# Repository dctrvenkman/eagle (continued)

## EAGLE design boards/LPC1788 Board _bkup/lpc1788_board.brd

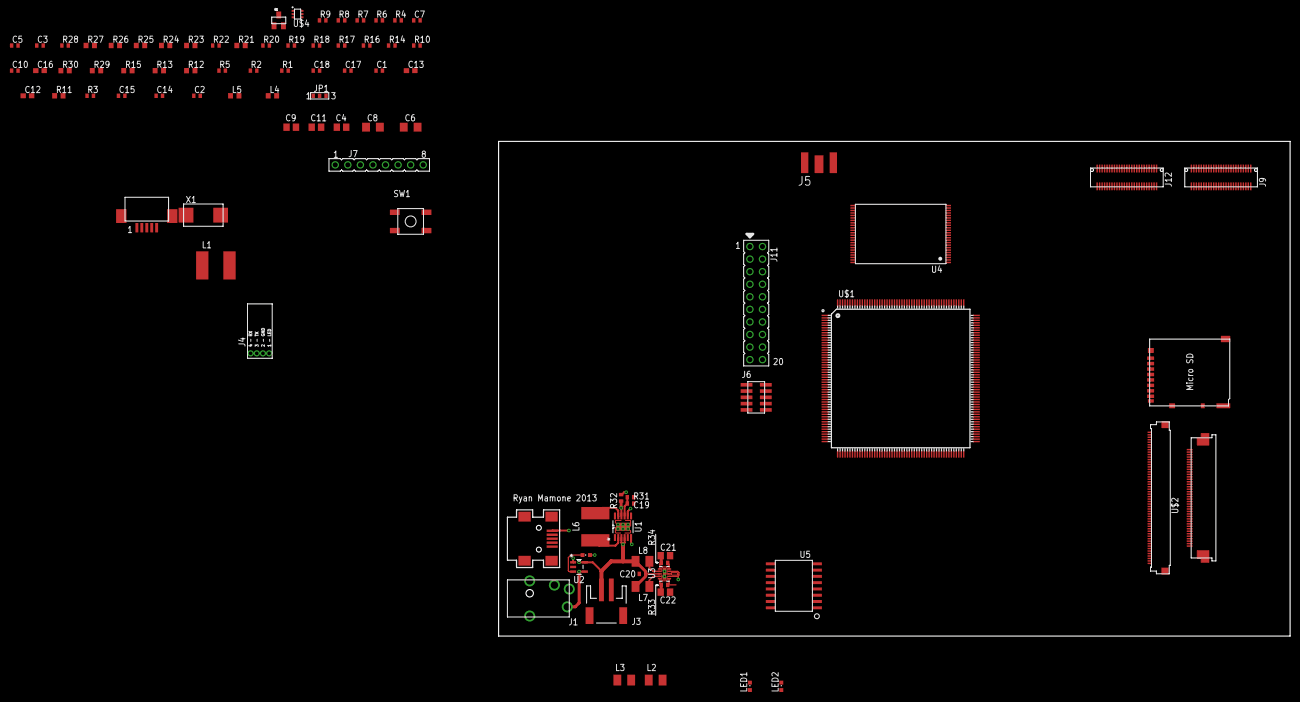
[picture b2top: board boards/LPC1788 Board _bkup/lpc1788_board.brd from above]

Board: 2 copper layers, 160.0 x 100.0 mm, 92 parts (0 on the bottom side), 154 nets.

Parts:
C1: 10uF; C0402
C2, C19: 100pF; C0402
C3, C5, C7, C10, C20: 1uF; C0402
C4: 22uF; C0805
C6: 100uF; C1206
C8: 330uF; C1206
C9, C11, C21, C22: 1uF; C0805
C12, C13: 18pF; C0603
C14, C15: 100nF; C0402
C16: .1uF; C0603
C17, C18: 18pF; C0402
J1: 5VDC; PJ-045
J2: SAMTEC_MUSB; MUSB-05-X-B-SM-A
J3: JST_2MM_SMT
J4: Console; 4-PIN_1.25MM
J5: SMA-J-P-X-ST-EM1
J6: JTAG; 10-PIN_5X2_.050IN_SMT
J7: JTAG; 8-PIN_SIP_.100IN
J8: NHD-4.3-480272EF; FCI_62684-402100ALF
J9, J12: DF12B-50DX_25X2_0.5MM
J10: MOLEX_527930570_5PIN_FFC_CONNECTOR; MOLEX_527930570
J11: 20PIN_10X2_.100IN; 20-PIN_10X2_.100IN
JP1: RESISTOR_JUMPER_0402
L1, L6: 4.7uH; NR6028
L2, L3, L7, L8: 15uH; L3225M
L4, L5: 470nH; 0603
LED1, LED2, LED3: CHG; CHIPLED_0603
Q1: MMBT2907; SOT23
R1, R32: 320k; R0402
R2: 182k; R0402
R3: 32.4k; R0402
R4, R16: 50; R0402
R5, R31: 499k; R0402
R6, R7, R33, R34: 10; R0402
R8, R9, R10: 0; R0402
R11: 100K; R0603
R12, R13, R29, R30: 4.7K; R0603
R14, R19, R20, R22, R28: 10k; R0402
R15: 1.5K; R0603
R17, R18: 33; R0402
R21: 0; R0603
R23, R24, R25, R26, R27: 10K; R0603
SW1: Reset; SMT_PUSHBUTTON
U1: LTC3127EMSEPBF; SOP65P490X110-13N
U2: MAX1551EZK+T; SOT95P275X110-5N
U3: LT3497EDDBTRMPBF; DFN300X200X80-11N
U4: CY62167_16MBIT_SRAM; TSOP48
U5: S25FL064P; SO3_016
U$1: LPC177X_8X-208; LQFP208
U$2: NHD-3.5-320240MF; MOLEX_51296-5494
U$3: DM3AT
U$4: NUP2202; SC-88
X1: 12MHz; 2-SMD_8MMX4.5MM

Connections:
!BLS0: U4.15, U$1.119
!BLS1: U4.14, U$1.139
!CS0: U4.26, U$1.187
!OE: U4.28, U$1.183
!WE: U4.11, U$1.179
+3V1: R32.2, U1.10
+3V3: C4.1, C6.1, C8.1, J4.1, J6.P$1, J8.P$4, J9.P$1, J9.P$2, J10.P$1, J11.1, J11.2, J11.3, J11.4, J12.P$1, J12.P$2, L4.1, L5.1, Q1.2, R1.2, R11.2, R12.1, R13.1, R14.1, R16.2, R19.1, R20.1, R21.2, R22.1, R23.1, R25.1, R26.1, R27.1, R28.1, R29.1, R30.1, U4.37, U5.P$2, U$1.15, U$1.26, U$1.60, U$1.71, U$1.86, U$1.89, U$1.112, U$1.125, U$1.146, U$1.165, U$1.174, U$1.181, U$1.198, U$2.P$41, U$2.P$42, U$3.VDD
+VBAT: C1.1, C7.1, C10.1, L2.1, L3.1, R4.2
+VBAT1: C20.1, J3.2, L7.1, L8.1, U1.3, U1.4, U2.5, U3.8
+VUSB: C5.1, U$4.P$5
+VUSB1: J2.1, U2.1
/RESET: C16.1, J6.P$10, J7.6, R11.1, SW1.P$1, SW1.P$2, U$1.35
A0: U4.25, U$1.75
A1: U4.24, U$1.79
A2: U4.23, U$1.83
A3: U4.22, U$1.97
A4: U4.21, U$1.103
A5: U4.20, U$1.107
A6: U4.19, U$1.113
A7: U4.18, U$1.121
A8: U4.8, U$1.127
A9: U4.7, U$1.131
A10: U4.6, U$1.135
A11: U4.5, U$1.145
A12: U4.4, U$1.149
A13: U4.3, U$1.155
A14: U4.2, U$1.159
A15: U4.1, U$1.173
A16: U4.48, U$1.101
A17: U4.17, U$1.104
A18: U4.16, U$1.105
A19: U4.9, U$1.111
B0: J8.P$21, U$1.160, U$2.P$12
B1: J8.P$22, U$1.158, U$2.P$13
B2: J8.P$23, U$1.106, U$2.P$14
B3: J8.P$24, U$1.102, U$2.P$15
B4: J8.P$25, U$1.82, U$2.P$16
B5: J8.P$26, U$1.88, U$2.P$17
B6: J8.P$27, U$1.90, U$2.P$18
B7: J8.P$28, U$1.92, U$2.P$19
D0: U4.29, U$1.197
D1: U4.31, U$1.201
D2: U4.33, U$1.207
D3: U4.35, U$1.3
D4: U4.38, U$1.13
D5: U4.40, U$1.17
D6: U4.42, U$1.23
D7: U4.44, U$1.27
D8: U4.30, U$1.191
D9: U4.32, U$1.199
D10: U4.34, U$1.205
D11: U4.36, U$1.208
D12: U4.39, U$1.1
D13: U4.41, U$1.7
D14: U4.43, U$1.21
D15: U4.45, U$1.28
EXT_UART_RX: J11.16, U$1.100
EXT_UART_TX: J11.14, U$1.98
G0: J8.P$13, U$1.164, U$2.P$20
G1: J8.P$14, U$1.162, U$2.P$21
G2: J8.P$15, U$1.170, U$2.P$22
G3: J8.P$16, U$1.176, U$2.P$23
G4: J8.P$17, U$1.74, U$2.P$24
G5: J8.P$18, U$1.76, U$2.P$25
G6: J8.P$19, U$1.78, U$2.P$26
G7: J8.P$20, U$1.80, U$2.P$27
GND: C1.2, C2.2, C3.2, C4.2, C5.2, C6.2, C7.2, C8.2, C9.2, C10.2, C11.2, C12.2, C13.2, C14.2, C15.2, C16.2, C17.2, C18.2, J4.2, J5.G@1, J6.P$3, J6.P$5, J6.P$9, J7.8, J8.P$1, J8.P$3, J8.P$29, J8.P$36, J9.P$49, J9.P$50, J10.P$5, J11.17, J11.18, J11.19, J11.20, J12.P$49, J12.P$50, R2.1, R3.1, R5.1, R24.2, SW1.P$3, SW1.P$4, U4.27, U4.46, U5.P$10, U$1.22, U$1.32, U$1.33, U$1.63, U$1.77, U$1.84, U$1.93, U$1.114, U$1.133, U$1.148, U$1.169, U$1.172, U$1.189, U$1.200, U$2.P$1, U$2.P$2, U$2.P$53, U$2.P$54, U$3.DET_B, U$3.VSS, U$4.P$2
GND1: C19.2, C20.2, C21.2, C22.2, J1.2, J1.3, J2.5, J3.1, R31.1, U1.1, U1.5, U1.7, U1.12, U1.13, U2.2, U3.3, U3.11
KEY_I2C_SCL: J10.P$3, R30.2, U$1.48
KEY_I2C_SDA: J10.P$2, R29.2, U$1.50
KEY_INT: J10.P$4, U$1.61
LCD_DCLK: J8.P$30, U$1.150, U$2.P$38
LCD_ENAB_M: J8.P$34, R8.1, U$1.142
LCD_FP: J8.P$33, U$1.144, U$2.P$37
LCD_LE: R9.1, U$1.152
LCD_LP: J8.P$32, U$1.140, U$2.P$36
LCD_PWR: R10.1, U$1.154
LED1_PWR: J8.P$2, JP1.1, R6.1, U$2.P$3
LED2_PWR: JP1.3, R7.1
LED+1: JP1.2, U$2.P$4
unnamed: R1.1, R2.2
unnamed: C9.1, R6.2
unnamed: C2.1, R5.2
unnamed: LED1.A, R4.1
unnamed: R8.2, U$2.P$52
unnamed: R9.2, U$2.P$50
unnamed: C11.1, R7.2
unnamed: R10.2, U$2.P$51
unnamed: C12.1, U$1.46, X1.2
unnamed: C13.1, U$1.44, X1.1
unnamed: C14.1, L4.2, U$1.20
unnamed: C15.1, L5.2, U$1.24
unnamed: R18.1, U$4.P$6
unnamed: R17.1, U$4.P$1
unnamed: Q1.3, R15.2
unnamed: Q1.1, U$1.69
unnamed: LED2.A, R16.1
unnamed: LED2.C, U$1.45
unnamed: J4.3, U$1.94
unnamed: J4.4, U$1.96
unnamed: J5.1, U$1.12
unnamed: R19.2, U4.12
unnamed: R20.2, U4.47
unnamed: J11.13, U$1.206
unnamed: R22.2, U5.P$9
unnamed: J11.7, U$1.30
unnamed: R28.2, U5.P$1
unnamed: J11.5, U$1.9
unnamed: J7.1, R21.1
unnamed: R32.1, U1.8
unnamed: C19.1, R31.2, U1.9
unnamed: LED3.C, U2.3
unnamed: L6.2, U1.2
unnamed: L6.1, U1.11
unnamed: C22.1, R33.2, U3.10
unnamed: R33.1, U3.1
unnamed: C21.1, R34.2, U3.6
unnamed: L7.2, U3.9
unnamed: L8.2, U3.7
unnamed: U3.2, U3.4
R0: J8.P$5, U$1.168, U$2.P$28
R1: J8.P$6, U$1.166, U$2.P$29
R2: J8.P$7, U$1.134, U$2.P$30
R3: J8.P$8, U$1.132, U$2.P$31
R4: J8.P$9, U$1.138, U$2.P$32
R5: J8.P$10, U$1.136, U$2.P$33
R6: J8.P$11, U$1.70, U$2.P$34
R7: J8.P$12, U$1.72, U$2.P$35
S$1: R34.1, U3.5
SCL: J11.11, R13.2, U$1.141
SDA: J11.9, R12.2, U$1.117
SD_CLK: U$1.122, U$3.CLK
SD_CMD: U$1.120, U$3.CMD
SD_DAT_0: U$1.116, U$3.DAT0
SD_DAT_1: U$1.153, U$3.DAT1
SD_DAT_2: U$1.163, U$3.DAT2
SD_DAT_3: U$1.157, U$3.CD/DAT3
SD_DET: R14.2, U$3.DET_A
SPI_CS: J11.12, U$1.190
SPI_FLASH_CS: U5.P$7, U$1.130
SPI_FLASH_MISO: U5.P$8, U$1.126
SPI_FLASH_MOSI: U5.P$15, U$1.124
SPI_FLASH_SCK: U5.P$16, U$1.128
SPI_MISO: J11.10, U$1.192
SPI_MOSI: J11.8, U$1.194
SPI_SCK: J11.6, U$1.196
TCK/SWDCLK: J6.P$4, J7.3, R24.1, U$1.10
TDI: J6.P$8, J7.5, R26.2, U$1.4
TDO/SWO: J6.P$6, J7.4, R25.2, U$1.2
TMS/SWDIO: J6.P$2, J7.2, R23.2, U$1.6
TRST: R27.2, U$1.8
USB_D+: C17.1, R15.1, R17.2, U$1.51
USB_D-: C18.1, R18.2, U$1.52
V+1: J1.1, U2.4

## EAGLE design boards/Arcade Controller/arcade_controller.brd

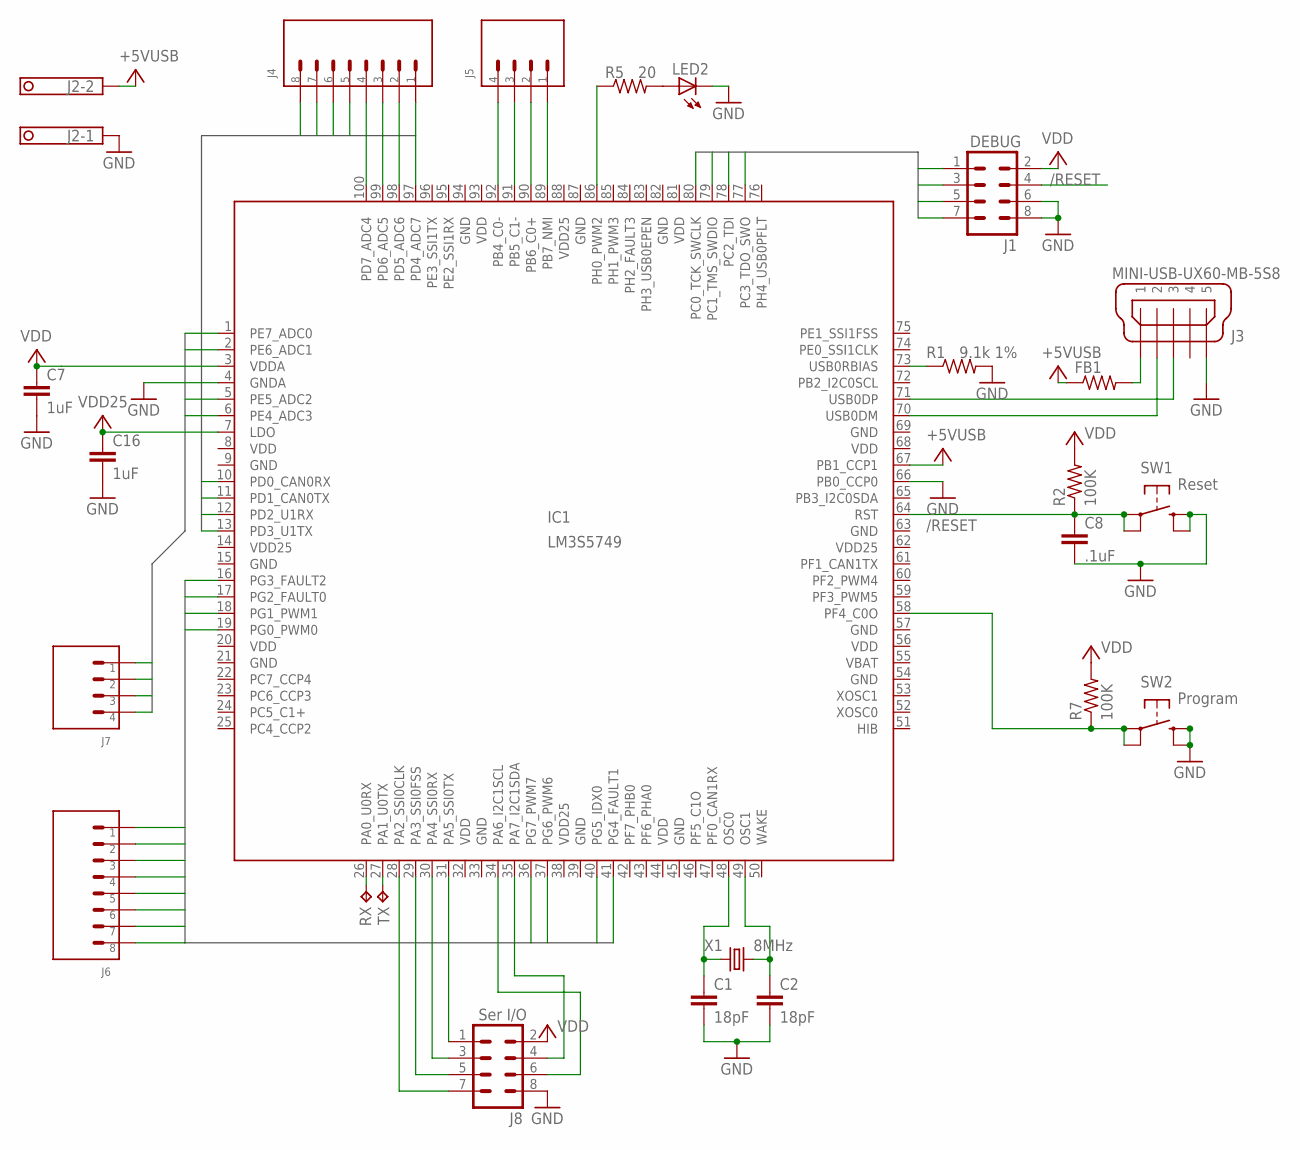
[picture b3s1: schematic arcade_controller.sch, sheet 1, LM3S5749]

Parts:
C1, C2: 18pF; C0603
C7, C16: 1uF; C0603
C8: .1uF; C0603
FB1: 0; R0805
IC1: LM3S5749; LQFP-100
J1: DEBUG; HEADER_.100IN_8PIN_4X2
J2: 1751248
J3: MINI-USB-UX60-MB-5S8; UX60-MB-5S8
J4, J6: PTSM_1771088
J5, J7: PTSM_1702474
J8: Ser I/O; HEADER_.100IN_8PIN_4X2
LED2: LEDCHIPLED_0603; CHIPLED_0603
R1: 9.1k 1%; R0603
R2, R7: 100K; R0603
R5: 20; R0603
RX: TPTP10R; TP10R
SW1: Reset; SMT_PUSHBUTTON
SW2: Program; SMT_PUSHBUTTON
TX: TPTP10R; TP10R
X1: 8MHz; 2-SMD_8MMX4.5MM

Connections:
/PROG: IC1.58 (PF4_C0O), R7.1, SW2.P$1 (P1), SW2.P$2
/RESET: C8.1, IC1.64 (RST), J1.4, R2.1, SW1.P$1 (P1), SW1.P$2
GND: C1.2, C2.2, C7.2, C8.2, C16.2, IC1.4 (GNDA), IC1.9 (GND), IC1.15 (GND), IC1.21 (GND), IC1.33 (GND), IC1.39 (GND), IC1.45 (GND), IC1.54 (GND), IC1.57 (GND), IC1.63 (GND), IC1.66 (PB0_CCP0), IC1.69 (GND), IC1.82 (GND), IC1.87 (GND), IC1.94 (GND), J1.6, J1.8, J2.1, J3.5, J8.8, LED2.C, R1.2, SW1.P$3 (S1), SW1.P$4 (S), SW2.P$3 (S1), SW2.P$4 (S); also elsewhere on the board
unnamed: IC1.73 (USB0RBIAS), R1.1
unnamed: C1.1, IC1.48 (OSC0), X1.1
unnamed: C2.1, IC1.49 (OSC1), X1.2
unnamed: IC1.26 (PA0_U0RX), RX.TP
unnamed: IC1.27 (PA1_U0TX), TX.TP
unnamed: FB1.2, J3.1
unnamed 10: FB1.1, IC1.67 (PB1_CCP1), J2.2; also elsewhere on the board
unnamed: IC1.89 (PB7_NMI), J5.P$1 (S1)
unnamed: IC1.90 (PB6_C0+), J5.P$2 (S2)
unnamed: IC1.91 (PB5_C1-), J5.P$3 (S3)
unnamed: IC1.92 (PB4_C0-), J5.P$4 (S4)
unnamed: IC1.86 (PH0_PWM2), R5.1
unnamed: IC1.31 (PA5_SSI0TX), J8.1
unnamed: LED2.A, R5.2
unnamed: IC1.30 (PA4_SSI0RX), J8.3
unnamed: IC1.71 (USB0DP), J3.3
unnamed: IC1.70 (USB0DM), J3.2
unnamed: IC1.29 (PA3_SSI0FSS), J8.5
unnamed: IC1.28 (PA2_SSI0CLK), J8.7
unnamed: IC1.35 (PA7_I2C1SDA), J8.4
unnamed: IC1.34 (PA6_I2C1SCL), J8.6
PD0: IC1.10 (PD0_CAN0RX), J4.P$1 (S1)
PD1: IC1.11 (PD1_CAN0TX), J4.P$2 (S2)
PD2: IC1.12 (PD2_U1RX), J4.P$3 (S3)
PD3: IC1.13 (PD3_U1TX), J4.P$4 (S4)
PD4: IC1.97 (PD4_ADC7), J4.P$5 (S5)
PD5: IC1.98 (PD5_ADC6), J4.P$6 (S6)
PD6: IC1.99 (PD6_ADC5), J4.P$7 (S7)
PD7: IC1.100 (PD7_ADC4), J4.P$8 (S8)
PE4: IC1.6 (PE4_ADC3), J7.P$4 (S4)
PE5: IC1.5 (PE5_ADC2), J7.P$3 (S3)
PE6: IC1.2 (PE6_ADC1), J7.P$2 (S2)
PE7: IC1.1 (PE7_ADC0), J7.P$1 (S1)
PG0: IC1.19 (PG0_PWM0), J6.P$8 (S8)
PG1: IC1.18 (PG1_PWM1), J6.P$7 (S7)
PG2: IC1.17 (PG2_FAULT0), J6.P$6 (S6)
PG3: IC1.16 (PG3_FAULT2), J6.P$5 (S5)
PG4: IC1.41 (PG4_FAULT1), J6.P$4 (S4)
PG5: IC1.40 (PG5_IDX0), J6.P$3 (S3)
PG6: IC1.37 (PG6_PWM6), J6.P$2 (S2)
PG7: IC1.36 (PG7_PWM7), J6.P$1 (S1)
TCK: IC1.80 (PC0_TCK_SWCLK), J1.1
TDI: IC1.78 (PC2_TDI), J1.5
TDO: IC1.77 (PC3_TDO_SWO), J1.7
TMS: IC1.79 (PC1_TMS_SWDIO), J1.3
VDD: C7.1, IC1.3 (VDDA), IC1.8 (VDD), IC1.20 (VDD), IC1.32 (VDD), IC1.44 (VDD), IC1.56 (VDD), IC1.68 (VDD), IC1.81 (VDD), IC1.93 (VDD), J1.2, J8.2, R2.2, R7.2; also elsewhere on the board
VDD25: C16.1, IC1.7 (LDO), IC1.14 (VDD25), IC1.38 (VDD25), IC1.62 (VDD25), IC1.88 (VDD25); also elsewhere on the board

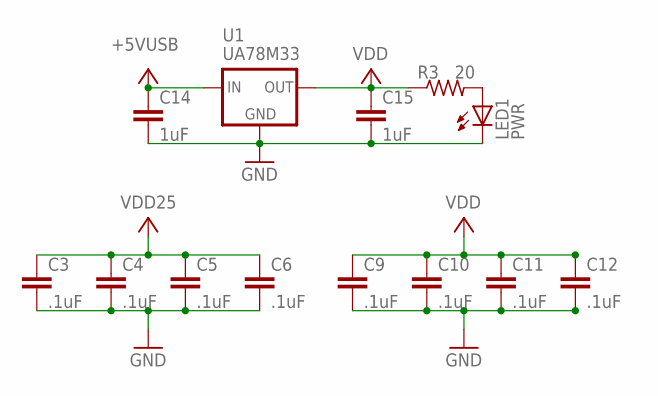
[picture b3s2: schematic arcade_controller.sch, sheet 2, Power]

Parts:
C3, C4, C5, C6, C9, C10, C11, C12: .1uF; C0603
C14, C15: 1uF; C0603
LED1: PWR; CHIPLED_0603
R3: 20; R0603
U1: UA78M33; SOT-223

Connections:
GND: C3.2, C4.2, C5.2, C6.2, C9.2, C10.2, C11.2, C12.2, C14.2, C15.2, LED1.C, U1.2 (GND), U1.4 (GND); also elsewhere on the board
unnamed: LED1.A, R3.2
unnamed 10: C14.1, U1.1 (IN); also elsewhere on the board
VDD: C9.1, C10.1, C11.1, C12.1, C15.1, R3.1, U1.3 (OUT); also elsewhere on the board
VDD25: C3.1, C4.1, C5.1, C6.1; also elsewhere on the board

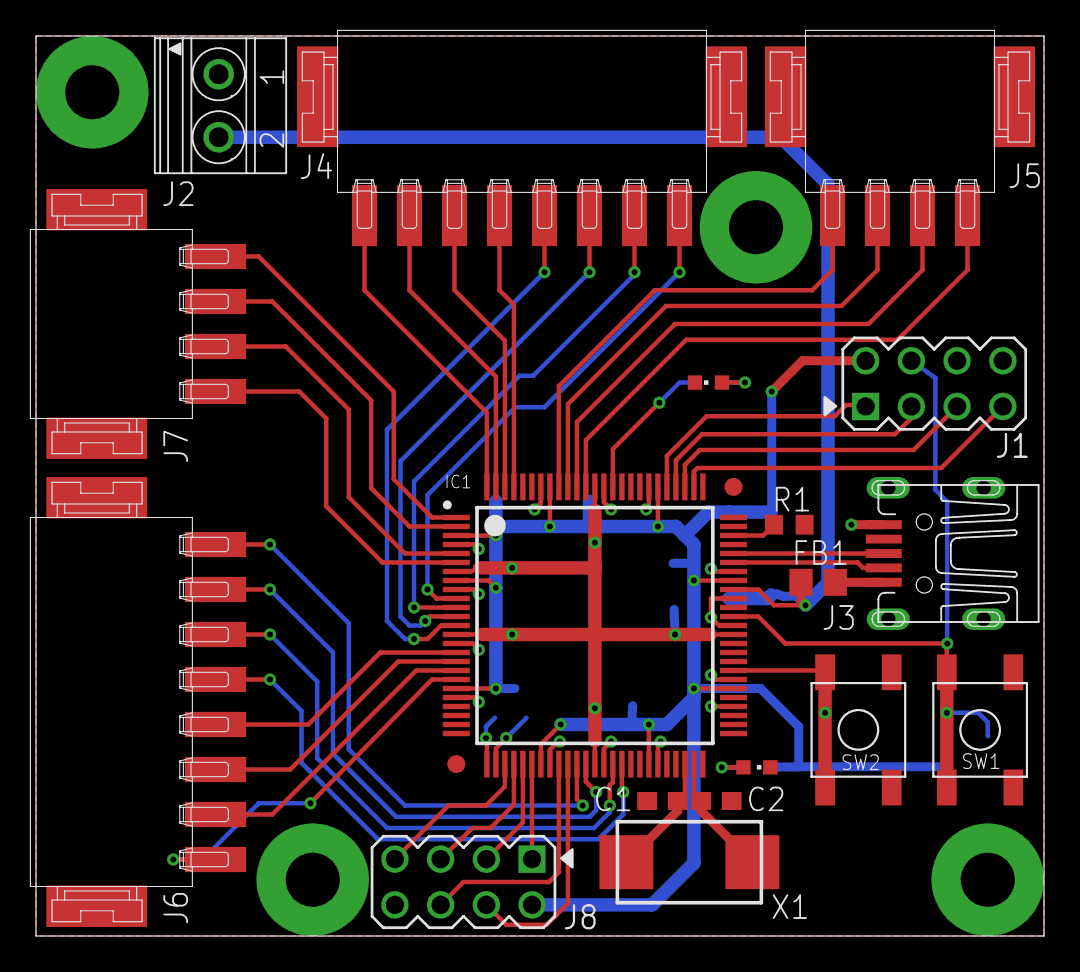
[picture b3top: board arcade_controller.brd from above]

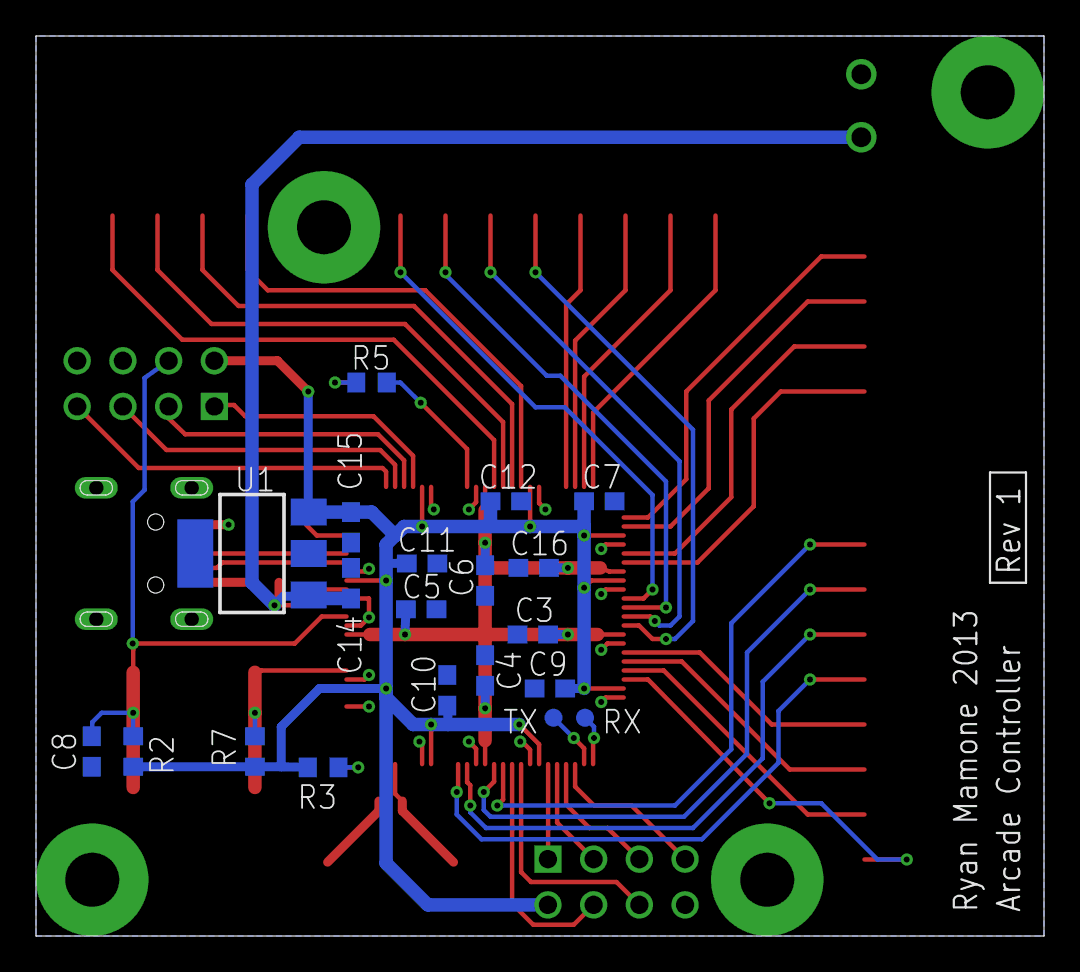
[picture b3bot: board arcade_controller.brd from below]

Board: 2 copper layers, 56.0 x 50.0 mm, 38 parts (20 on the bottom side), 51 nets.

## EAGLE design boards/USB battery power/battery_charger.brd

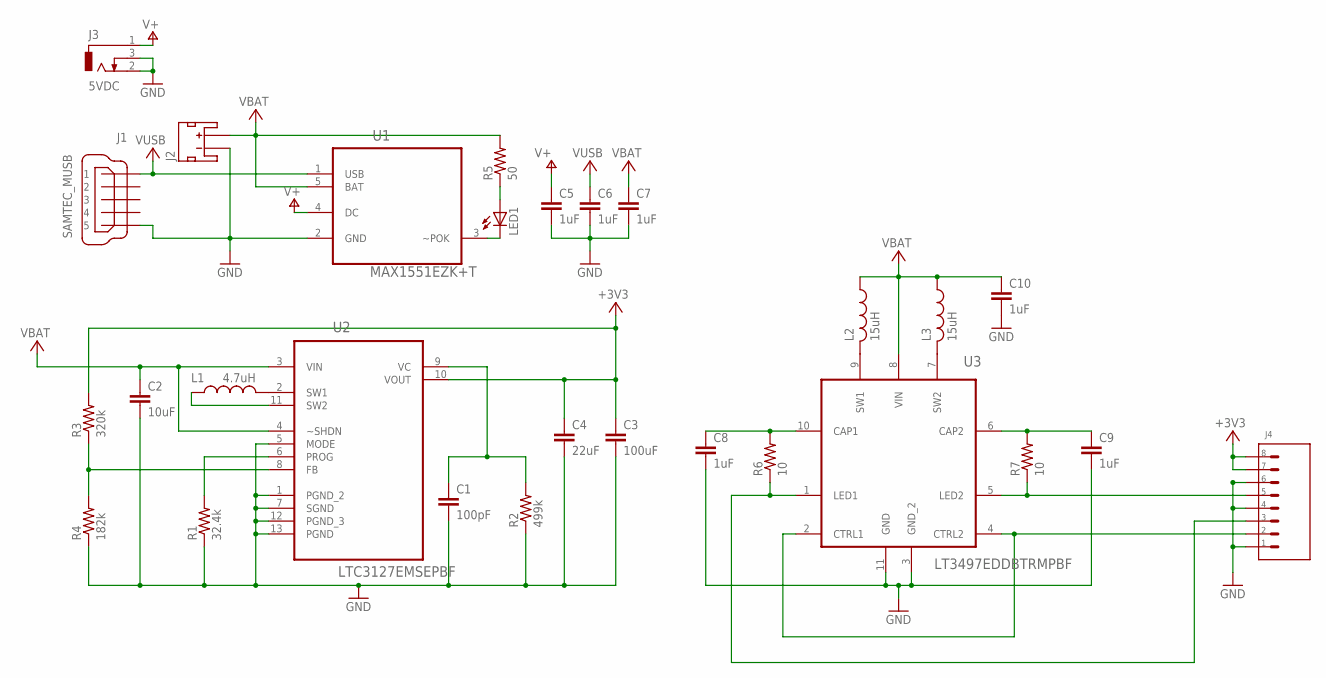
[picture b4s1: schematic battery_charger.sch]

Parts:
C1: 100pF; C0402
C2: 10uF; C0402
C3: 100uF; C1206
C4: 22uF; C0805
C5, C6, C7, C10: 1uF; C0402
C8, C9: 1uF; C0805
J1: SAMTEC_MUSB; MUSB-05-X-B-SM-A
J2: JST_2MM_SMT
J3: 5VDC; PJ-045
J4: IO; 8-PIN_SIP_.100IN
L1: 4.7uH; NR6028
L2, L3: 15uH; L3225M
LED1: CHG; CHIPLED_0603
R1: 32.4k; R0402
R2: 499k; R0402
R3: 320k; R0402
R4: 182k; R0402
R5: 50; R0402
R6, R7: 10; R0402
U1: MAX1551EZK+T; SOT95P275X110-5N
U2: LTC3127EMSEPBF; SOP65P490X110-13N
U3: LT3497EDDBTRMPBF; DFN300X200X80-11N

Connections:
+3V3: C3.1, C4.1, J4.7 (S7), J4.8 (S8), R3.2, U2.10 (VOUT)
+VBAT: C2.1, C7.1, C10.1, J2.2 (+), L2.1, L3.1, R5.2, U1.5 (BAT), U2.3 (VIN), U2.4 (~SHDN), U3.8 (VIN)
+VUSB: C6.1, J1.1, U1.1 (USB)
GND: C1.2, C2.2, C3.2, C4.2, C5.2, C6.2, C7.2, C8.2, C9.2, C10.2, J1.5, J2.1 (-), J3.2, J3.3, J4.1 (S1), J4.4 (S4), J4.6 (S6), R1.1, R2.1, R4.1, U1.2 (GND), U2.1 (PGND_2), U2.5 (MODE), U2.7 (SGND), U2.12 (PGND_3), U2.13 (PGND), U3.3 (GND_2), U3.11 (GND)
unnamed: R1.2, U2.6 (PROG)
unnamed: R3.1, R4.2, U2.8 (FB)
unnamed: L1.2, U2.2 (SW1)
unnamed: L1.1, U2.11 (SW2)
unnamed: LED1.C, U1.3 (~POK)
unnamed: C8.1, R6.2, U3.10 (CAP1)
unnamed: C1.1, R2.2, U2.9 (VC)
unnamed: LED1.A, R5.1
unnamed: J4.3 (S3), R6.1, U3.1 (LED1)
unnamed: J4.5 (S5), R7.1, U3.5 (LED2)
unnamed: C9.1, R7.2, U3.6 (CAP2)
unnamed: L2.2, U3.9 (SW1)
unnamed: L3.2, U3.7 (SW2)
unnamed: J4.2 (S2), U3.2 (CTRL1), U3.4 (CTRL2)
V+: C5.1, J3.1, U1.4 (DC)

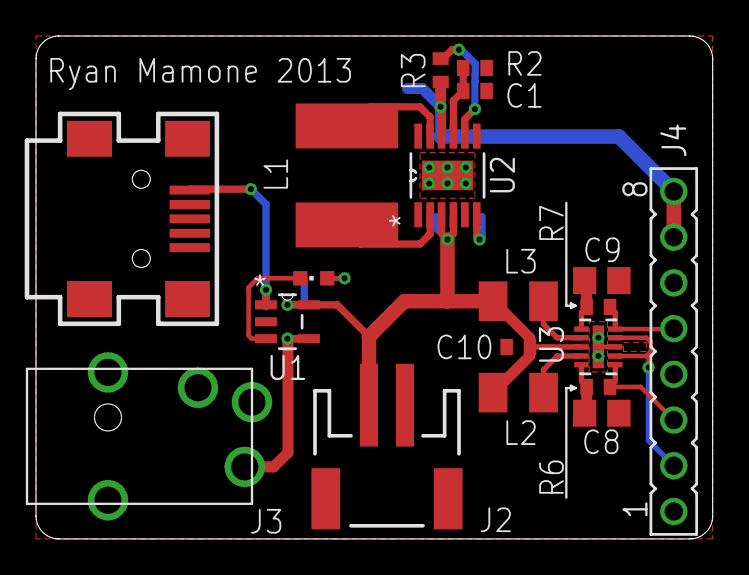
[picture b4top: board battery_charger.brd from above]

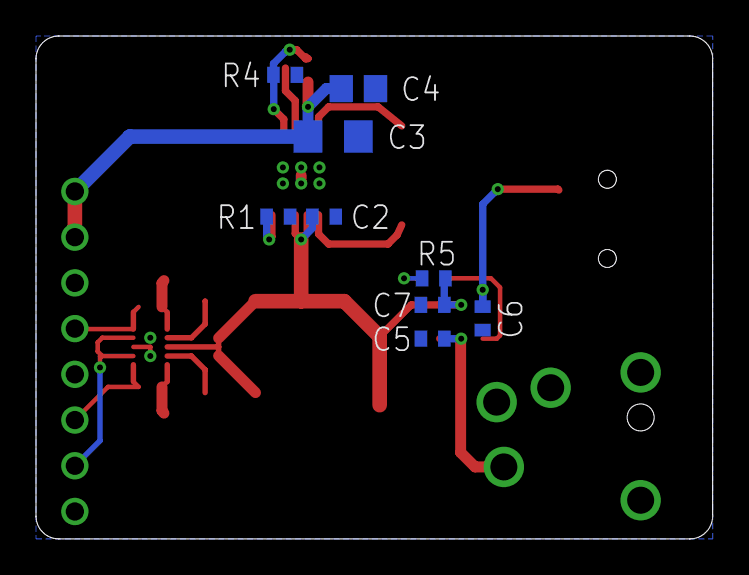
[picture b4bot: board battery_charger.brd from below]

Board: 2 copper layers, 37.6 x 27.9 mm, 28 parts (9 on the bottom side), 19 nets.

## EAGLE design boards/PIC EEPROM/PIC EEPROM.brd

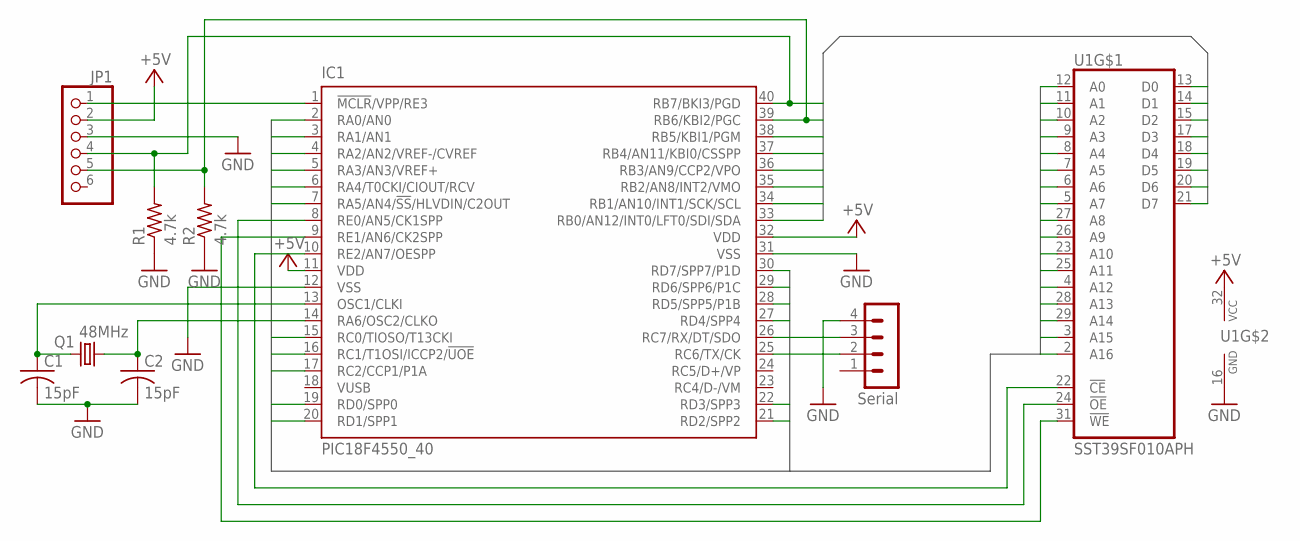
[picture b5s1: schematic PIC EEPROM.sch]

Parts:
C1, C2: 15pF; C0603
IC1: PIC18F4550_40; DIL40
JP1: ICSP; 1X06/90
Q1: 48MHz; HC49U-V
R1, R2: 4.7k; R0603
SV1: Serial; MA04-1
U1: SST39SF010APH; PDIP32

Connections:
+5V: IC1.11 (VDD), IC1.32 (VDD), JP1.2, U1.32 (VCC)
A0: IC1.19 (RD0/SPP0), U1.12 (A0)
A1: IC1.20 (RD1/SPP1), U1.11 (A1)
A2: IC1.21 (RD2/SPP2), U1.10 (A2)
A3: IC1.22 (RD3/SPP3), U1.9 (A3)
A4: IC1.27 (RD4/SPP4), U1.8 (A4)
A5: IC1.28 (RD5/SPP5/P1B), U1.7 (A5)
A6: IC1.29 (RD6/SPP6/P1C), U1.6 (A6)
A7: IC1.30 (RD7/SPP7/P1D), U1.5 (A7)
A8: IC1.2 (RA0/AN0), U1.27 (A8)
A9: IC1.3 (RA1/AN1), U1.26 (A9)
A10: IC1.4 (RA2/AN2/VREF-/CVREF), U1.23 (A10)
A11: IC1.5 (RA3/AN3/VREF+), U1.25 (A11)
A12: IC1.6 (RA4/T0CKI/CIOUT/RCV), U1.4 (A12)
A13: IC1.7 (RA5/AN4/!SS!/HLVDIN/C2OUT), U1.28 (A13)
A14: IC1.15 (RC0/TIOSO/T13CKI), U1.29 (A14)
A15: IC1.16 (RC1/T1OSI/ICCP2/!UOE), U1.3 (A15)
A16: IC1.17 (RC2/CCP1/P1A), U1.2 (A16)
D0: IC1.33 (RB0/AN12/INT0/LFT0/SDI/SDA), U1.13 (D0)
D1: IC1.34 (RB1/AN10/INT1/SCK/SCL), U1.14 (D1)
D2: IC1.35 (RB2/AN8/INT2/VMO), U1.15 (D2)
D3: IC1.36 (RB3/AN9/CCP2/VPO), U1.17 (D3)
D4: IC1.37 (RB4/AN11/KBI0/CSSPP), U1.18 (D4)
D5: IC1.38 (RB5/KBI1/PGM), U1.19 (D5)
D6: IC1.39 (RB6/KBI2/PGC), JP1.5, R2.2, U1.20 (D6)
D7: IC1.40 (RB7/BKI3/PGD), JP1.4, R1.2, U1.21 (D7)
GND: C1.2, C2.2, IC1.12 (VSS), IC1.31 (VSS), JP1.3, R1.1, R2.1, SV1.4, U1.16 (GND)
unnamed: IC1.1 (!MCLR!/VPP/RE3), JP1.1
unnamed: C1.1, IC1.13 (OSC1/CLKI), Q1.1
unnamed: IC1.10 (RE2/AN7/OESPP), U1.22 (!CE)
unnamed: IC1.8 (RE0/AN5/CK1SPP), U1.24 (!OE)
unnamed: IC1.9 (RE1/AN6/CK2SPP), U1.31 (!WE)
unnamed: C2.1, IC1.14 (RA6/OSC2/CLKO), Q1.2
unnamed: IC1.25 (RC6/TX/CK), SV1.2
unnamed: IC1.26 (RC7/RX/DT/SDO), SV1.3

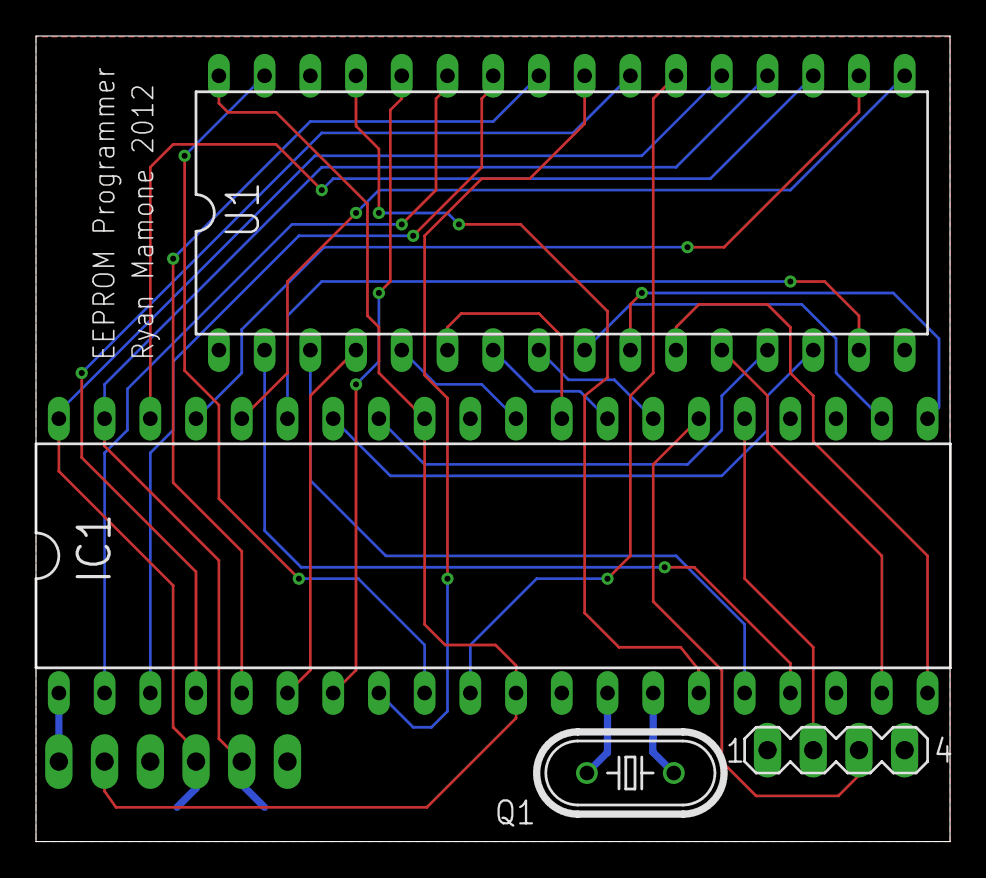
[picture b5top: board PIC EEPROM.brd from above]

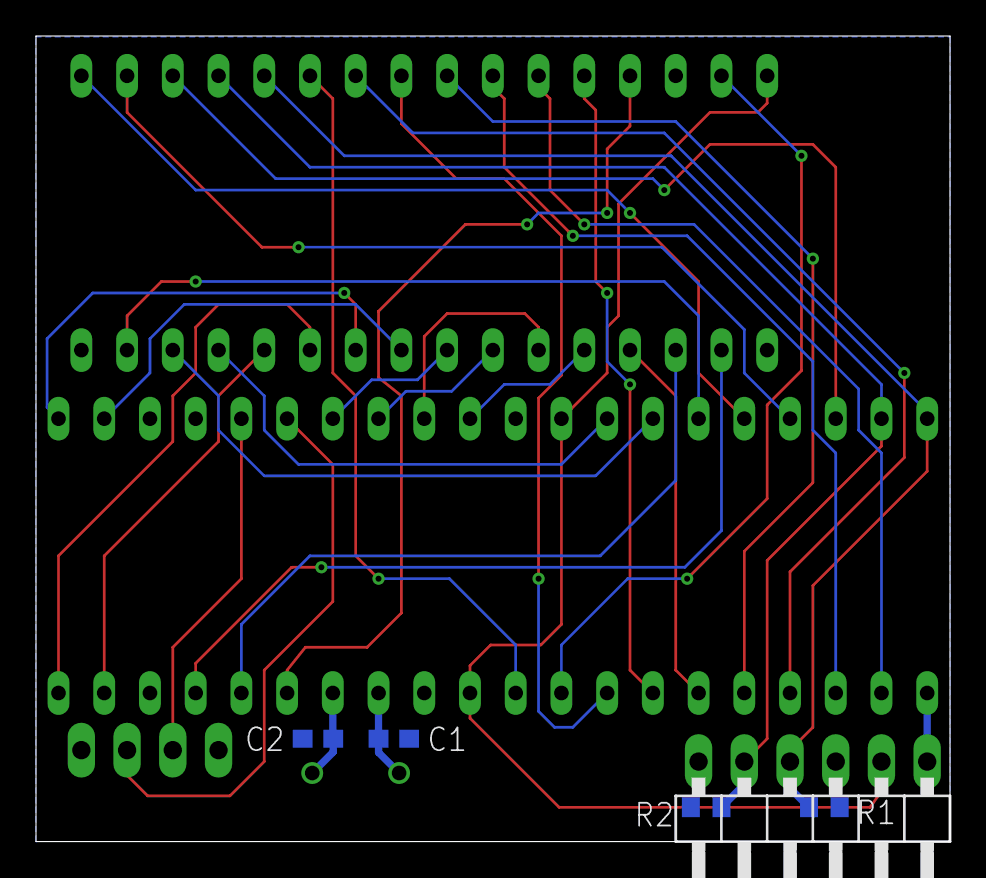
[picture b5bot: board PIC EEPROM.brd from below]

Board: 2 copper layers, 50.8 x 44.8 mm, 9 parts (5 on the bottom side), 35 nets.

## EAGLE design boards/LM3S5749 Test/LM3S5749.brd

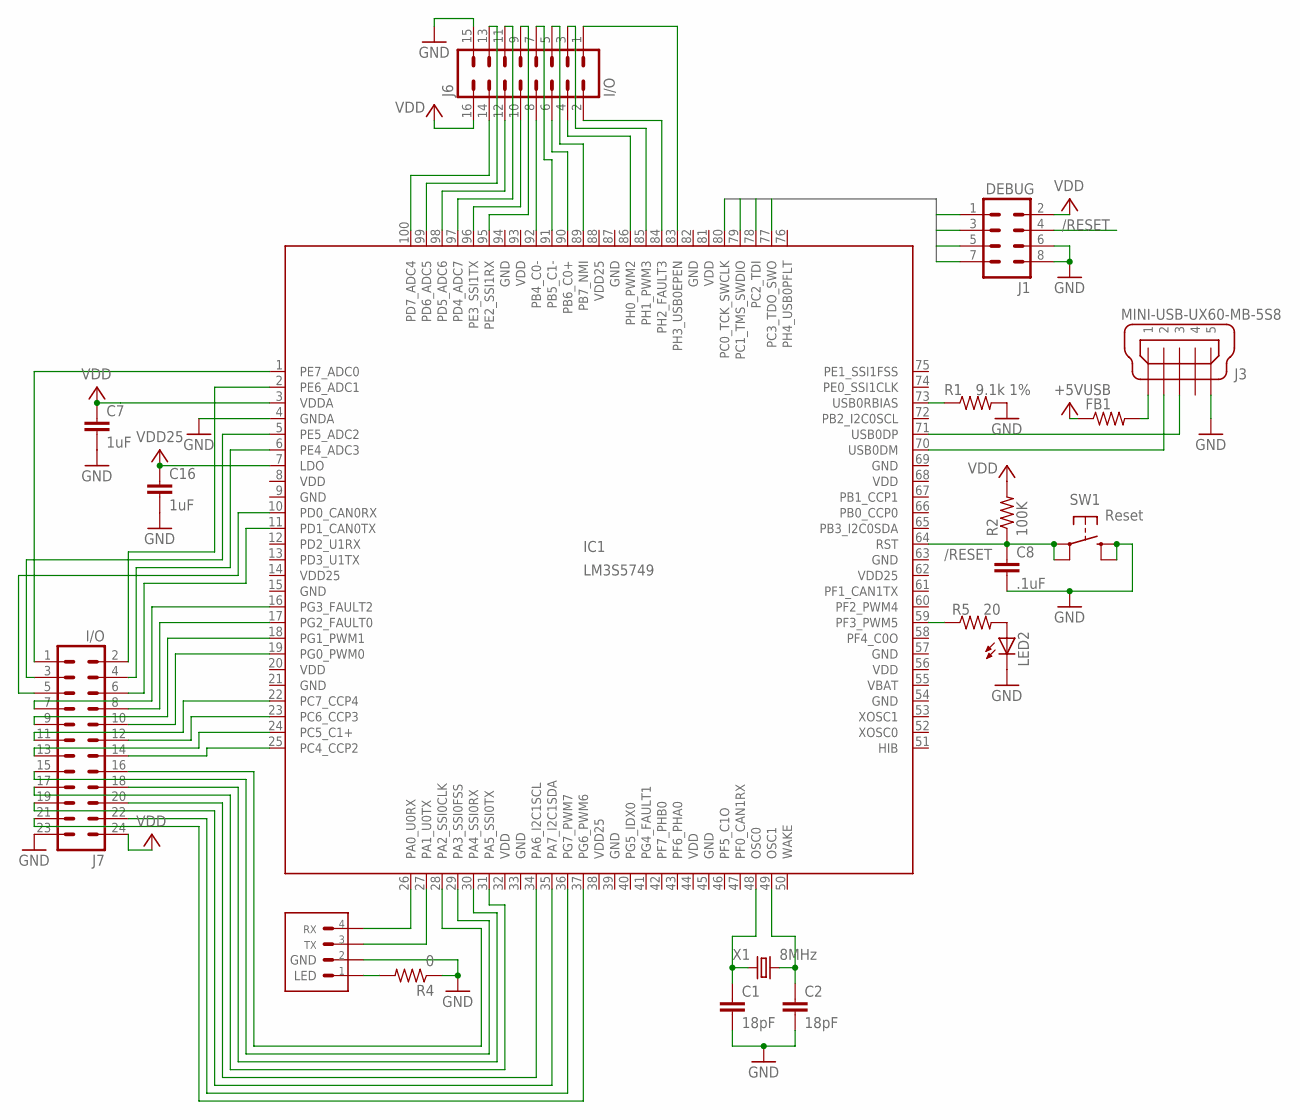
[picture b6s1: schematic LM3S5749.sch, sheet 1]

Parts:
C1, C2: 18pF; C0603
C7, C16: 1uF; C0603
C8: .1uF; C0603
FB1: 0; R0805
IC1: LM3S5749; LQFP-100
J1: DEBUG; HEADER_.100IN_8PIN_4X2
J3: MINI-USB-UX60-MB-5S8; UX60-MB-5S8
J4: Serial; 4-PIN_1.25MM
J6: I/O; HEADER_.100IN_16PIN_8X2
J7: I/O; HEADER_.100IN_24PIN_D
LED2: LEDCHIPLED_0603; CHIPLED_0603
R1: 9.1k 1%; R0603
R2: 100K; R0603
R4: 0; R0603
R5: 20; R0603
SW1: Reset; SMT_PUSHBUTTON
X1: 8MHz; 2-SMD_8MMX4.5MM

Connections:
/RESET: C8.1, IC1.64 (RST), J1.4, R2.1, SW1.P$1 (P1), SW1.P$2
GND: C1.2, C2.2, C7.2, C8.2, C16.2, IC1.4 (GNDA), IC1.9 (GND), IC1.15 (GND), IC1.21 (GND), IC1.33 (GND), IC1.39 (GND), IC1.45 (GND), IC1.54 (GND), IC1.57 (GND), IC1.63 (GND), IC1.69 (GND), IC1.82 (GND), IC1.87 (GND), IC1.94 (GND), J1.6, J1.8, J3.5, J4.2 (S2), J6.15, J7.23, LED2.C, R1.2, R4.1, SW1.P$3 (S1), SW1.P$4 (S); also elsewhere on the board
unnamed: IC1.73 (USB0RBIAS), R1.1
unnamed: C1.1, IC1.48 (OSC0), X1.1
unnamed: C2.1, IC1.49 (OSC1), X1.2
unnamed: IC1.26 (PA0_U0RX), J4.4 (S4)
unnamed: IC1.27 (PA1_U0TX), J4.3 (S3)
unnamed: FB1.2, J3.1
unnamed 9: FB1.1; also elsewhere on the board
unnamed: IC1.16 (PG3_FAULT2), J7.7
unnamed: IC1.17 (PG2_FAULT0), J7.8
unnamed: IC1.18 (PG1_PWM1), J7.9
unnamed: IC1.19 (PG0_PWM0), J7.10
unnamed: IC1.36 (PG7_PWM7), J7.22
unnamed: IC1.37 (PG6_PWM6), J7.21
unnamed: LED2.A, R5.2
unnamed: IC1.59 (PF3_PWM5), R5.1
unnamed: IC1.71 (USB0DP), J3.3
unnamed: IC1.70 (USB0DM), J3.2
unnamed: IC1.28 (PA2_SSI0CLK), J7.16
unnamed: IC1.29 (PA3_SSI0FSS), J7.15
unnamed: IC1.30 (PA4_SSI0RX), J7.18
unnamed: IC1.31 (PA5_SSI0TX), J7.17
unnamed: IC1.34 (PA6_I2C1SCL), J7.20
unnamed: IC1.35 (PA7_I2C1SDA), J7.19
unnamed: J4.1 (S1), R4.2
unnamed: IC1.22 (PC7_CCP4), J7.11
unnamed: IC1.23 (PC6_CCP3), J7.12
unnamed: IC1.24 (PC5_C1+), J7.13
unnamed: IC1.25 (PC4_CCP2), J7.14
unnamed: IC1.83 (PH3_USB0EPEN), J6.1
unnamed: IC1.84 (PH2_FAULT3), J6.2
unnamed: IC1.85 (PH1_PWM3), J6.3
unnamed: IC1.86 (PH0_PWM2), J6.4
unnamed: IC1.89 (PB7_NMI), J6.5
unnamed: IC1.90 (PB6_C0+), J6.6
unnamed: IC1.91 (PB5_C1-), J6.7
unnamed: IC1.92 (PB4_C0-), J6.8
unnamed: IC1.95 (PE2_SSI1RX), J6.9
unnamed: IC1.96 (PE3_SSI1TX), J6.10
unnamed: IC1.97 (PD4_ADC7), J6.11
unnamed: IC1.98 (PD5_ADC6), J6.12
unnamed: IC1.99 (PD6_ADC5), J6.13
unnamed: IC1.100 (PD7_ADC4), J6.14
unnamed: IC1.1 (PE7_ADC0), J7.1
unnamed: IC1.2 (PE6_ADC1), J7.2
unnamed: IC1.5 (PE5_ADC2), J7.3
unnamed: IC1.6 (PE4_ADC3), J7.4
unnamed: IC1.10 (PD0_CAN0RX), J7.5
unnamed: IC1.11 (PD1_CAN0TX), J7.6
TCK: IC1.80 (PC0_TCK_SWCLK), J1.1
TDI: IC1.78 (PC2_TDI), J1.5
TDO: IC1.77 (PC3_TDO_SWO), J1.7
TMS: IC1.79 (PC1_TMS_SWDIO), J1.3
VDD: C7.1, IC1.3 (VDDA), IC1.8 (VDD), IC1.20 (VDD), IC1.32 (VDD), IC1.44 (VDD), IC1.56 (VDD), IC1.68 (VDD), IC1.81 (VDD), IC1.93 (VDD), J1.2, J6.16, J7.24, R2.2; also elsewhere on the board
VDD25: C16.1, IC1.7 (LDO), IC1.14 (VDD25), IC1.38 (VDD25), IC1.62 (VDD25), IC1.88 (VDD25); also elsewhere on the board

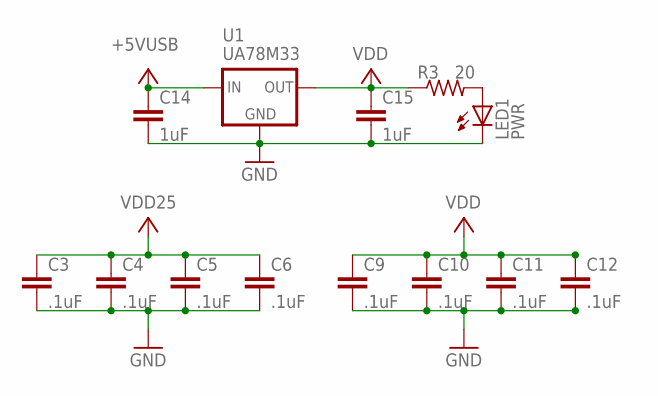
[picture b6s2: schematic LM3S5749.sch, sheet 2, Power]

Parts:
C3, C4, C5, C6, C9, C10, C11, C12: .1uF; C0603
C14, C15: 1uF; C0603
LED1: PWR; CHIPLED_0603
R3: 20; R0603
U1: UA78M33; SOT-223

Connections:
GND: C3.2, C4.2, C5.2, C6.2, C9.2, C10.2, C11.2, C12.2, C14.2, C15.2, LED1.C, U1.2 (GND), U1.4 (GND); also elsewhere on the board
unnamed: LED1.A, R3.2
unnamed 9: C14.1, U1.1 (IN); also elsewhere on the board
VDD: C9.1, C10.1, C11.1, C12.1, C15.1, R3.1, U1.3 (OUT); also elsewhere on the board
VDD25: C3.1, C4.1, C5.1, C6.1; also elsewhere on the board

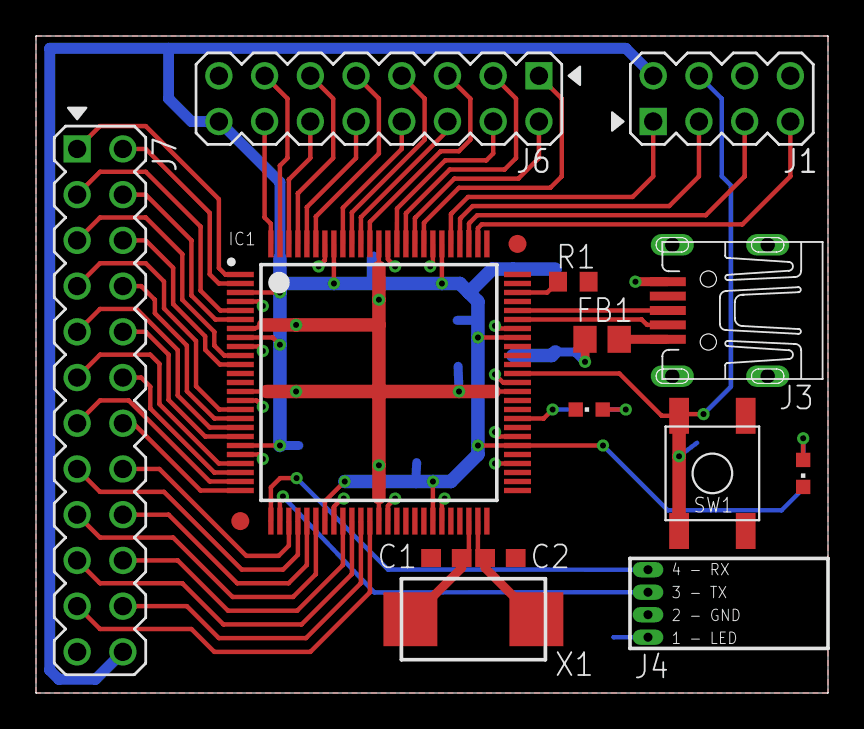
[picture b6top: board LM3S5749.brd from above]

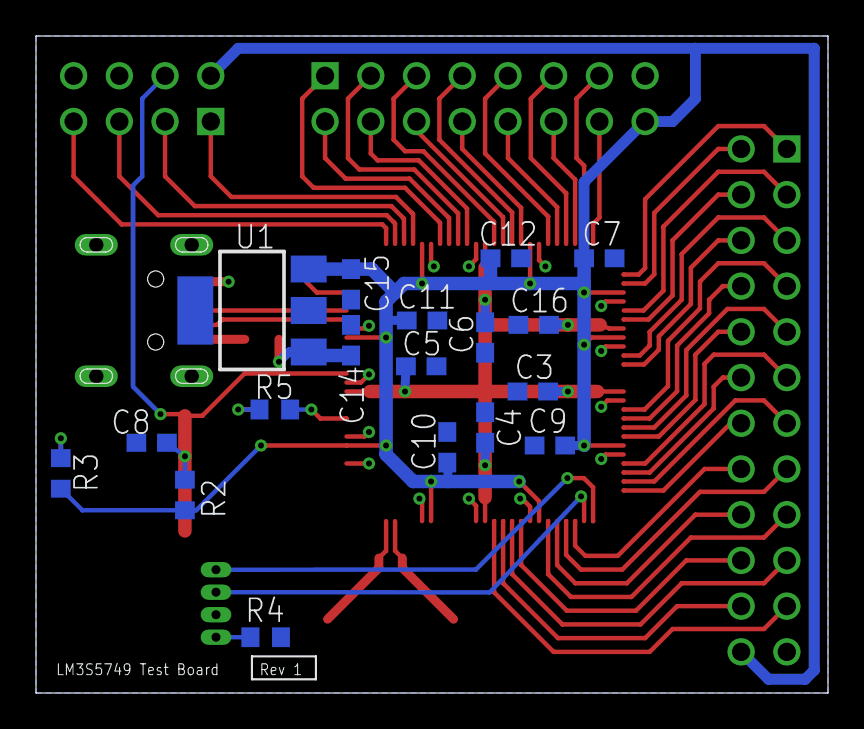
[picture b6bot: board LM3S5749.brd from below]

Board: 2 copper layers, 44.0 x 36.5 mm, 32 parts (18 on the bottom side), 57 nets.

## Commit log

2013-04-13 Initial Delivery
2013-04-13 Added board files
2013-06-05 Arcade Controller Board
2013-06-11 stuff
2013-07-11 Battery Charger test board
2013-07-12 I dunno
2013-12-16 Start of LPC1788 Board
2014-01-17 Continued work on LPC1788 board
2014-01-20 more lpc1788 board changes
2014-02-11 more layout of LPC1788 board
2014-03-03 Finishing up LCP1788 board
2014-03-10 switch to sdram
2014-03-18 LPC1788 Board Rev 1
2014-07-13 Storing local changes before upgrading to eagle 6.6.0
